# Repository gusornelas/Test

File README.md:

# Test
This is a test to see how GitHub works.

In this repository there is a project that basically is a pin_extender created in Kicad.

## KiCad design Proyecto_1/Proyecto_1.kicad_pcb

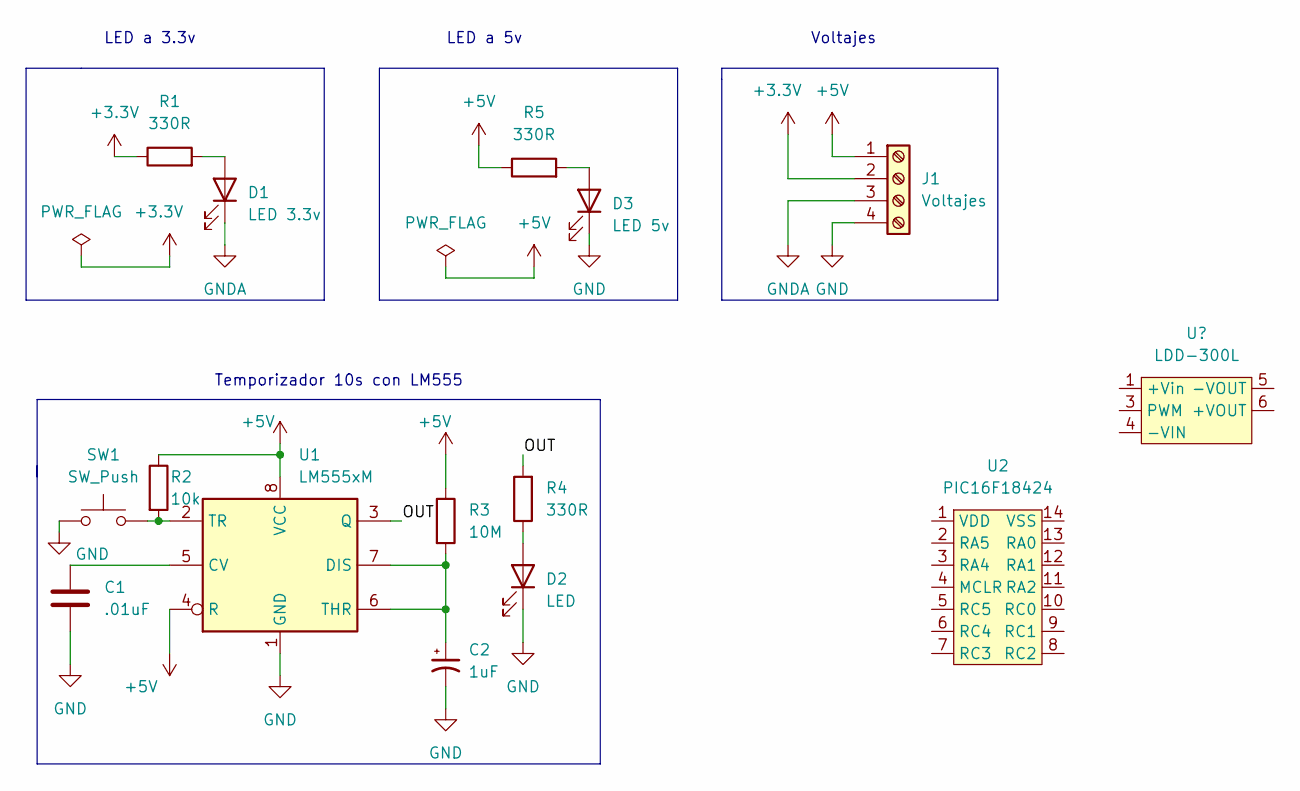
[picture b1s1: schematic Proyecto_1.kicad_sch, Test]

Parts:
C1: .01uF; C_Disc_D3.4mm_W2.1mm_P2.50mm
C2: 1uF; CP_Radial_D4.0mm_P2.00mm
D1: LED 3.3v; LED_D3.0mm
D2: LED; LED_D3.0mm
D3: LED 5v; LED_D3.0mm
J1: Voltajes; TerminalBlock_bornier-4_P5.08mm
R1, R4, R5: 330R; R_Axial_DIN0204_L3.6mm_D1.6mm_P7.62mm_Horizontal
R2: 10k; R_Axial_DIN0204_L3.6mm_D1.6mm_P7.62mm_Horizontal
R3: 10M; R_Axial_DIN0204_L3.6mm_D1.6mm_P7.62mm_Horizontal
SW1: SW_Push; SW_PUSH_6mm
U1: LM555xM; DIP-8_W10.16mm_LongPads
U2: PIC16F18424; SOIC-14_3.9x8.7mm_P1.27mm

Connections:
+3.3V: J1.2, R1.1
+5V: J1.1, R2.1, R3.1, R5.1, U1.4 (R), U1.8 (VCC)
/OUT: R4.2, U1.3 (Q)
GND: C1.2, C2.2, D2.1 (K), D3.1 (K), J1.4, SW1.1, U1.1 (GND)
GNDA: D1.1 (K), J1.3
unnamed: C2.1, R3.2, U1.6 (THR), U1.7 (DIS)
unnamed: D1.2 (A), R1.2
unnamed: D2.2 (A), R4.1
unnamed: D3.2 (A), R5.2
unnamed: R2.2, SW1.2, U1.2 (TR)
unnamed: C1.1, U1.5 (CV)

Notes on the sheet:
LED a 3.3v
LED a 5v
Voltajes
Temporizador 10s con LM555

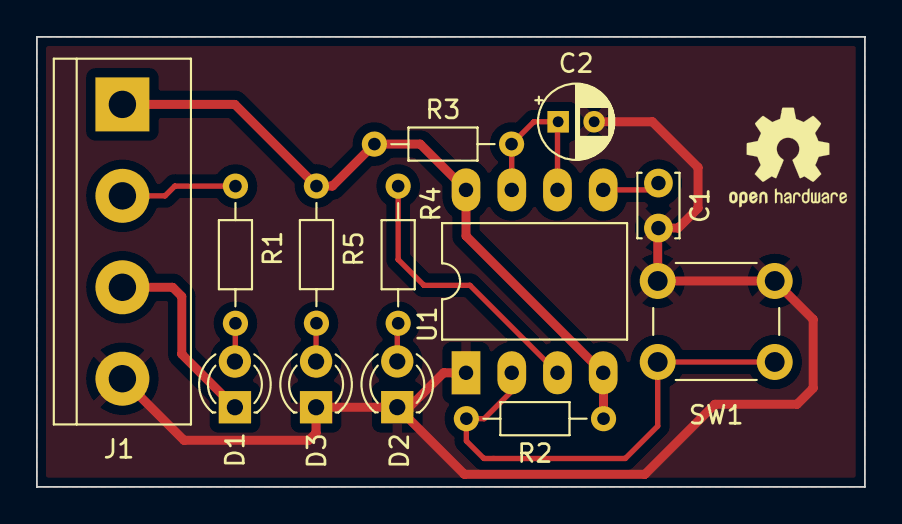
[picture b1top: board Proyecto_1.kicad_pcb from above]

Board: 2 copper layers, 46.0 x 25.0 mm, 13 parts (0 on the bottom side), 11 nets.

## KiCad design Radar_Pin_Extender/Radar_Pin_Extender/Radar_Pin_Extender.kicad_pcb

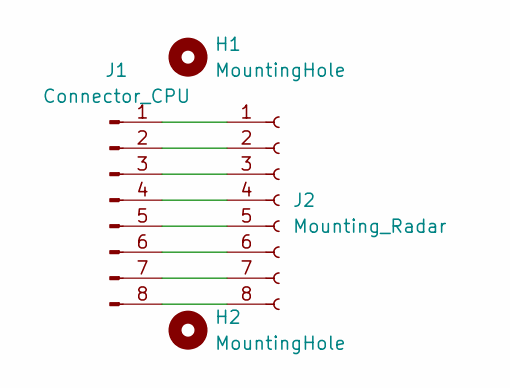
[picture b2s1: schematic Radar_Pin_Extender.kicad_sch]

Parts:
H1, H2: MountingHole; MountingHole_3.2mm_M3
J1: Connector_CPU; PinHeader_1x08_P2.54mm_Vertical
J2: Mounting_Radar; PinSocket_1x08_P2.54mm_Vertical

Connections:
unnamed: J1.1, J2.1
unnamed: J1.2, J2.2
unnamed: J1.3, J2.3
unnamed: J1.4, J2.4
unnamed: J1.5, J2.5
unnamed: J1.6, J2.6
unnamed: J1.7, J2.7
unnamed: J1.8, J2.8

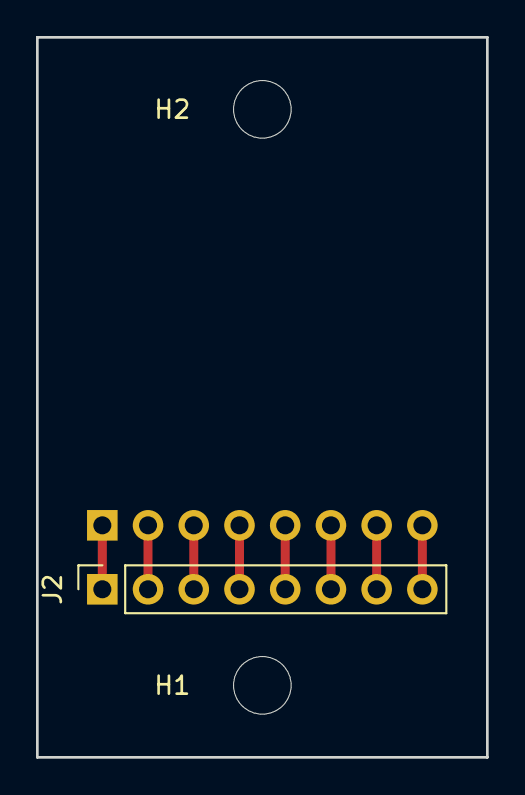
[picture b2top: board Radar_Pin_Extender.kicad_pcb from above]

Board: 2 copper layers, 25.0 x 40.0 mm, 4 parts (1 on the bottom side), 8 nets.
